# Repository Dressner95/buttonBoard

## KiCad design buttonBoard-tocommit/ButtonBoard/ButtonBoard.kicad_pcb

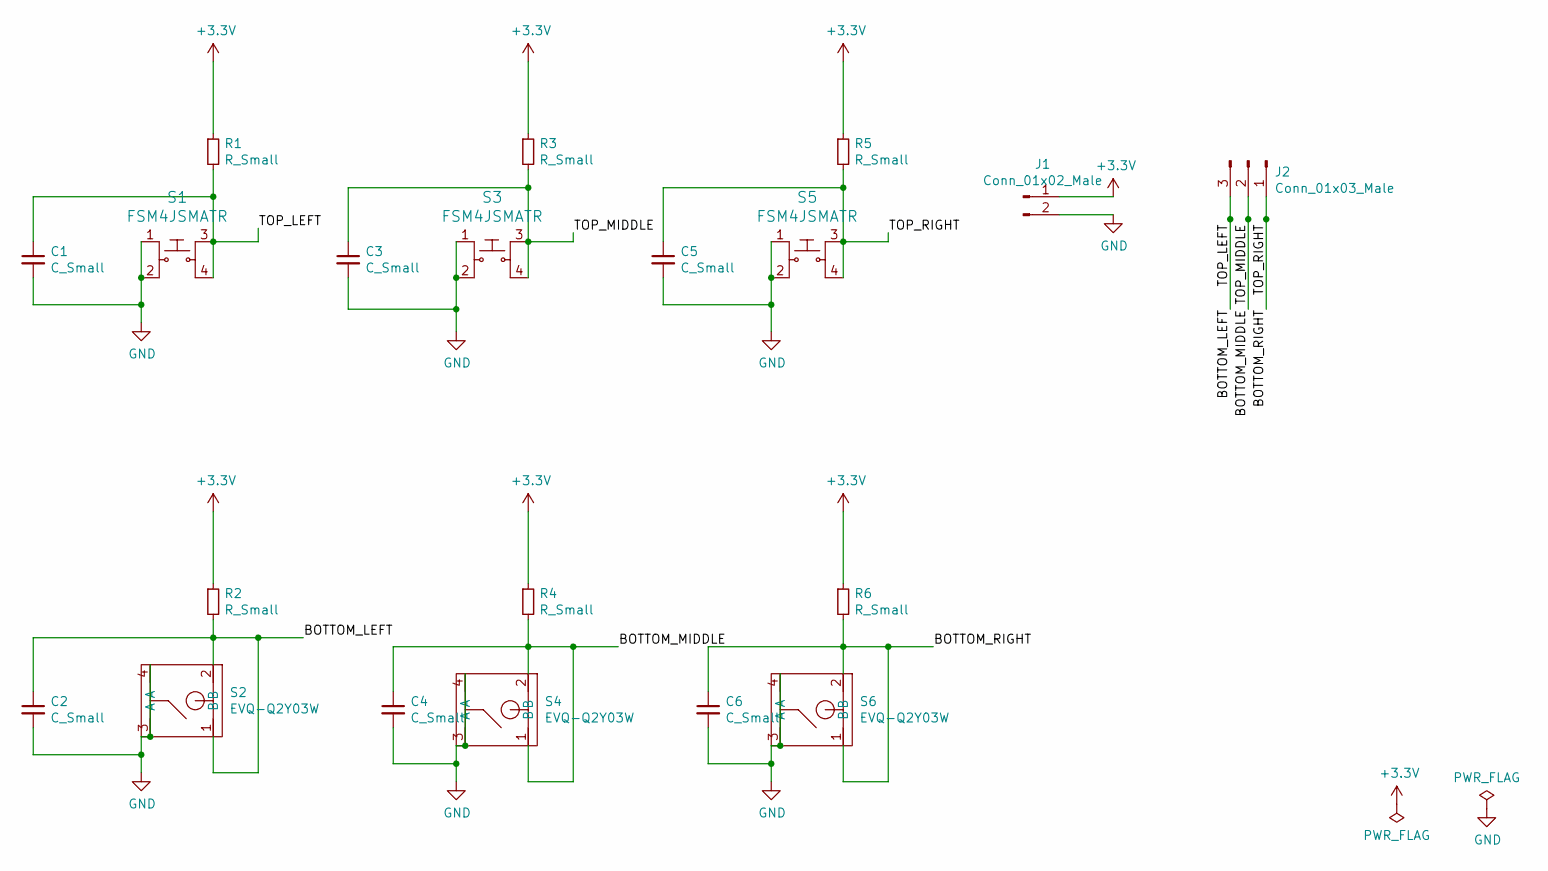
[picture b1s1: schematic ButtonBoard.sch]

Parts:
C1, C2, C3, C4, C5, C6: C_Small; C0805
J1: Conn_01x02_Male; H2-2.54
J2: Conn_01x03_Male; H3-2.54
R1, R2, R3, R4, R5, R6: R_Small; R0805
S1, S3, S5: FSM4JSMATR; Switch_Tactile_SMD_6x6mm; MPN FSM4JSMATR; Digi-Key_PN 450-1759-1-ND
S2, S4, S6: EVQ-Q2Y03W

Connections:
+3V3: J1.1, R1.1, R2.1, R3.1, R4.1, R5.1, R6.1; also elsewhere on the board
/BOTTOM_LEFT: C1.1, C2.1, J2.3, R1.2, R2.2, S1.3, S1.4, S2.1 (B), S2.2 (B); also elsewhere on the board
/BOTTOM_MIDDLE: C3.1, C4.1, J2.2, R3.2, R4.2, S3.3, S3.4, S4.1 (B), S4.2 (B); also elsewhere on the board
/BOTTOM_RIGHT: C5.1, C6.1, J2.1, R5.2, R6.2, S5.3, S5.4, S6.1 (B), S6.2 (B); also elsewhere on the board
GND: C1.2, C2.2, C3.2, C4.2, C5.2, C6.2, J1.2, S1.1, S1.2, S2.3 (A), S2.4 (A), S3.1, S3.2, S4.3 (A), S4.4 (A), S5.1, S5.2, S6.3 (A), S6.4 (A); also elsewhere on the board

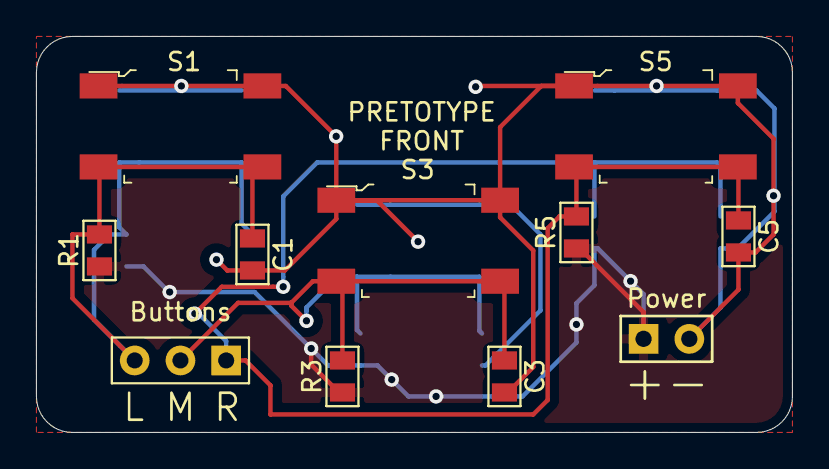
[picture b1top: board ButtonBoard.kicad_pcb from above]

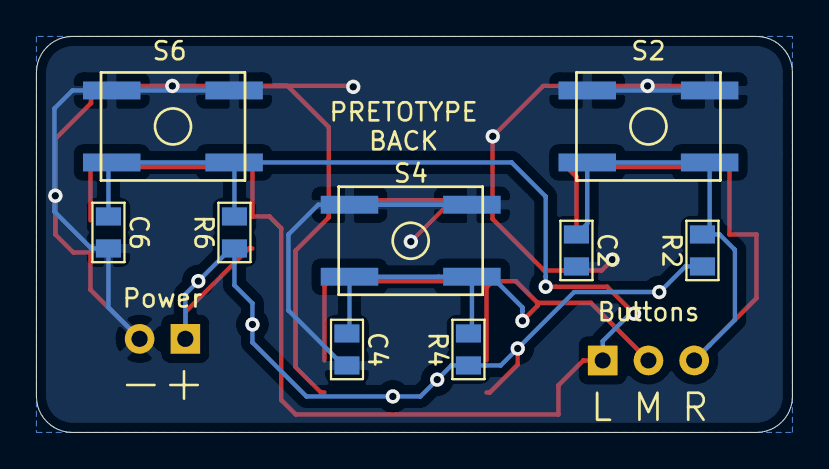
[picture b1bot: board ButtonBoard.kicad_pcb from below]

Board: 2 copper layers, 42.0 x 22.0 mm, 20 parts (9 on the bottom side), 5 nets.

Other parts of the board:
Buttons: Conn_01x03_Male; H3-2.54
Power: Conn_01x02_Male; H2-2.54

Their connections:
+3V3: Power.1; also elsewhere on the board
/BOTTOM_LEFT: Buttons.3; also elsewhere on the board
/BOTTOM_MIDDLE: Buttons.2; also elsewhere on the board
/BOTTOM_RIGHT: Buttons.1; also elsewhere on the board
GND: Power.2; also elsewhere on the board

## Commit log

2019-11-05 intial commit
